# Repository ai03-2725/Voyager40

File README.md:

# Voyager40
A compact, fully featured 40% PCB

[Supported layouts](http://www.keyboard-layout-editor.com/#/gists/b095690facf5e7ddff7d799d73baacf5)  

#### In light of recent claims that I am 100% liable for any of my open source PCBs, I am adding this disclaimer.
#### I provide these PCBs as a reference for designing keyboard PCBs. Using them within your projects will require a will to do research of one's own and to learn the workings of them, potentially fixing issues if they exist.
# I provide these PCBs without liability and without any guarantees regarding functionality, as expressed in the MIT license under which all of these PCBs are licensed.

### Features
* In-switch LED backlighting
* RGB underglow
* Decent amount of layout compatibility
* Over-current and static discharge protection
* Fully open-source

### The Voyager PCB Family
The Voyager PCBs offer fully featured PCBs fit for any keyboard, whether mass production or high-end.

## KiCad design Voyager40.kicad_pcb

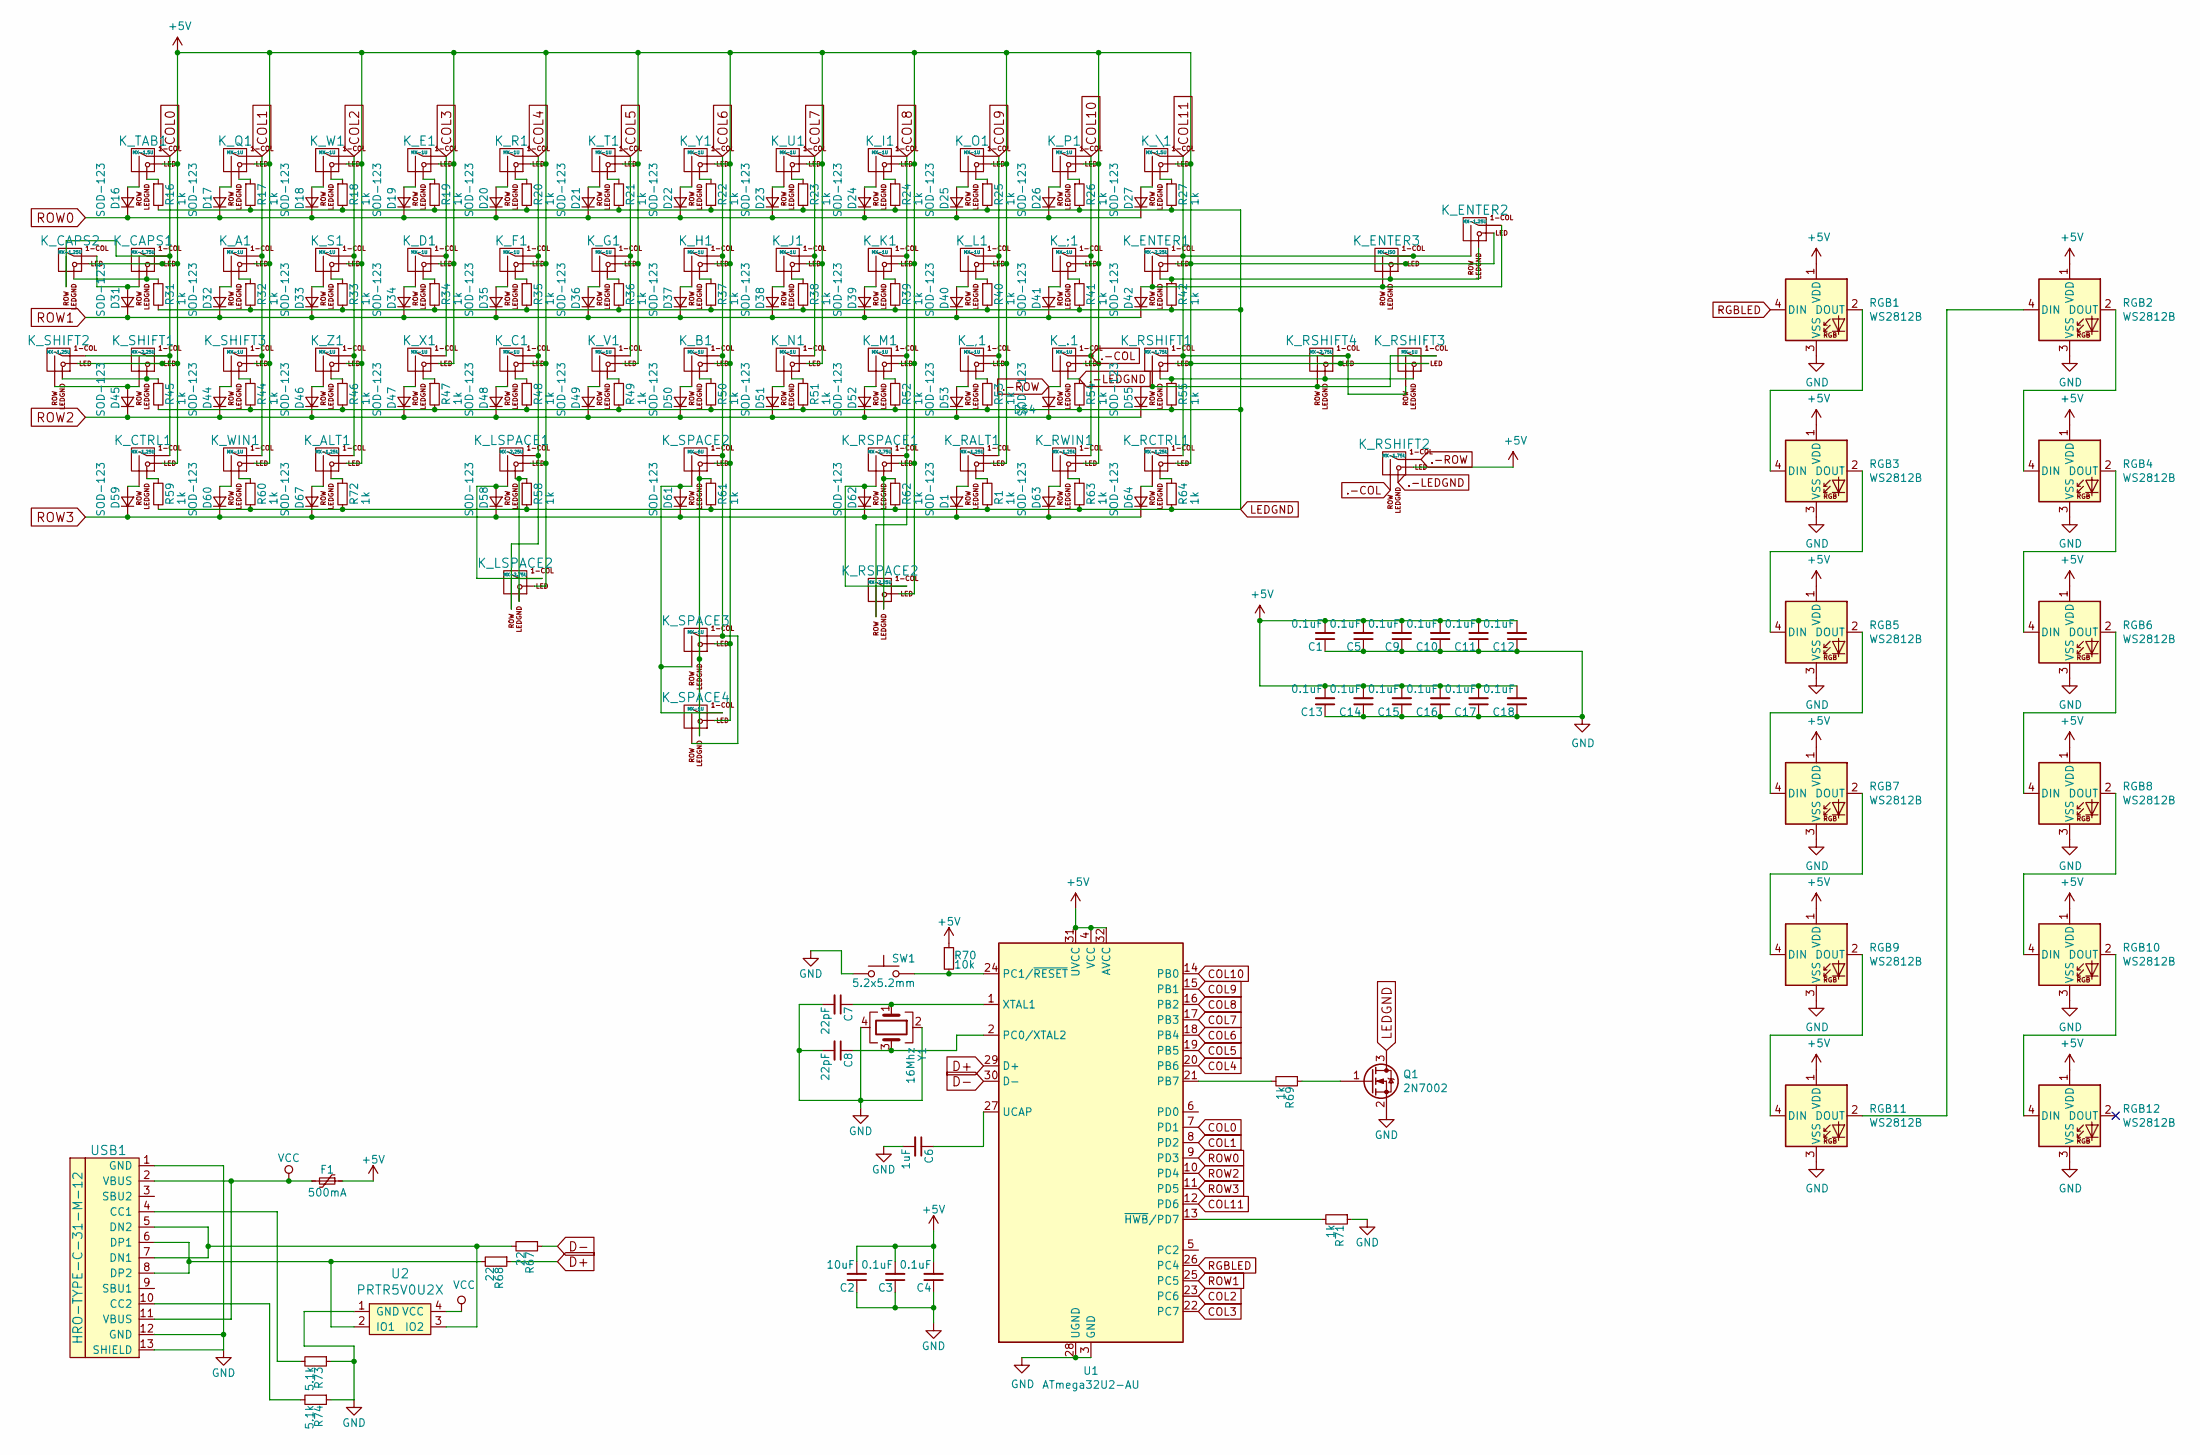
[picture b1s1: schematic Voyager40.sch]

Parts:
C1, C3, C4, C5, C9, C10, C11, C12, C13, C14, C15, C16, C17, C18: 0.1uF; C_0603
C2: 10uF; C_0603
C6: 1uF; C_0603
C7, C8: 22pF; C_0603
D1, D16, D17, D18, D19, D20, D21, D22, D23, D24, D25, D26, D27, D31, D32, D33, D34, D35, D36, D37, D38, D39, D40, D41, D42, D44, D45, D46, D47, D48, D49, D50, D51, D52, D53, D54, D55, D58, D59, D60, D61, D62, D63, D64, D67: SOD-123; D_SOD-123
F1: 500mA; Fuse_SMD1206_Reflow
K_,1: MX-1U
K_.1: MX-1U
K_;1: MX-1U
K_A1: MX-1U
K_ALT1: MX-1.25U
K_B1: MX-1U
K_C1: MX-1U
K_CAPS1: MX-1.75U
K_CAPS2: MX-1.25U; MX-1.25U-FLIPPED
K_CTRL1: MX-1.25U
K_D1: MX-1U
K_E1: MX-1U
K_ENTER1: MX-2.25U
K_ENTER2: MX-1.25U
K_ENTER3: MX-ISO; MX-ISO-ReversedStabilizers
K_F1: MX-1U
K_G1: MX-1U
K_H1: MX-1U
K_I1: MX-1U
K_J1: MX-1U
K_K1: MX-1U
K_L1: MX-1U
K_LSPACE1: MX-2.25U; MX-2.25U-ReversedStabilizers
K_LSPACE2: MX-2.75U; MX-2.75U-FLIPPED-ReversedStabilizers
K_M1: MX-1U
K_N1: MX-1U
K_O1: MX-1U
K_P1: MX-1U
K_Q1: MX-1U
K_R1: MX-1U
K_RALT1: MX-1.25U
K_RCTRL1: MX-1.25U
K_RSHIFT1, K_RSHIFT2: MX-1.75U
K_RSHIFT3: MX-1U
K_RSHIFT4: MX-2.75U
K_RSPACE1: MX-2.75U; MX-2.75U-ReversedStabilizers
K_RSPACE2: MX-2.25U; MX-2.25U-FLIPPED-ReversedStabilizers
K_RWIN1: MX-1.25U; MX-1U
K_S1: MX-1U
K_SHIFT1: MX-2.25U
K_SHIFT2: MX-1.25U
K_SHIFT3: MX-1U
K_SPACE2: MX-6U; MX-6U-ReversedStabilizers
K_SPACE3: MX-1U
K_SPACE4: MX-1U; MX-1U-FLIPPED
K_T1: MX-1U
K_TAB1: MX-1.5U
K_U1: MX-1U
K_V1: MX-1U
K_W1: MX-1U
K_WIN1: MX-1U
K_X1: MX-1U
K_Y1: MX-1U
K_Z1: MX-1U
K_\1: MX-1.5U
Q1: 2N7002; SOT-23
R1, R16, R17, R18, R19, R20, R21, R22, R23, R24, R25, R26, R27, R31, R32, R33, R34, R35, R36, R37, R38, R39, R40, R41, R42, R44, R45, R46, R47, R48, R49, R50, R51, R52, R53, R54, R55, R58, R59, R60, R61, R62, R63, R64, R69, R71, R72: 1k; R_0805
R67, R68: 22; R_0805
R70: 10k; R_0805
R73, R74: 5.1k; R_0805
RGB1, RGB2, RGB3, RGB4, RGB5, RGB6, RGB7, RGB8, RGB9, RGB10, RGB11, RGB12: WS2812B; LED_WS2812B-PLCC4
SW1: 5.2x5.2mm; SKQGADE010
U1: ATmega32U2-AU; QFN-32-1EP_5x5mm_Pitch0.5mm
U2: PRTR5V0U2X; SOT143B
USB1: HRO-TYPE-C-31-M-12; HRO-TYPE-C-31-M-12-Assembly
Y1: 16Mhz; Crystal_SMD_3225-4pin_3.2x2.5mm

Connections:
+5V: C1.2, C2.2, C3.2, C4.2, C5.2, C9.2, C10.2, C11.2, C12.2, C13.2, C14.2, C15.2, C16.2, C17.2, C18.2, F1.1, K_,1.3 (LED), K_.1.3 (LED), K_;1.3 (LED), K_A1.3 (LED), K_ALT1.3 (LED), K_B1.3 (LED), K_C1.3 (LED), K_CAPS1.3 (LED), K_CAPS2.3 (LED), K_CTRL1.3 (LED), K_D1.3 (LED), K_E1.3 (LED), K_ENTER1.3 (LED), K_ENTER2.3 (LED), K_ENTER3.3 (LED), K_F1.3 (LED), K_G1.3 (LED), K_H1.3 (LED), K_I1.3 (LED), K_J1.3 (LED), K_K1.3 (LED), K_L1.3 (LED), K_LSPACE1.3 (LED), K_LSPACE2.3 (LED), K_M1.3 (LED), K_N1.3 (LED), K_O1.3 (LED), K_P1.3 (LED), K_Q1.3 (LED), K_R1.3 (LED), K_RALT1.3 (LED), K_RCTRL1.3 (LED), K_RSHIFT1.3 (LED), K_RSHIFT2.3 (LED), K_RSHIFT3.3 (LED), K_RSHIFT4.3 (LED), K_RSPACE1.3 (LED), K_RSPACE2.3 (LED), K_RWIN1.3 (LED), K_S1.3 (LED), K_SHIFT1.3 (LED), K_SHIFT2.3 (LED), K_SHIFT3.3 (LED), K_SPACE2.3 (LED), K_SPACE3.3 (LED), K_SPACE4.3 (LED), K_T1.3 (LED), K_TAB1.3 (LED), K_U1.3 (LED), K_V1.3 (LED), K_W1.3 (LED), K_WIN1.3 (LED), K_X1.3 (LED), K_Y1.3 (LED), K_Z1.3 (LED), K_\1.3 (LED), R70.1, RGB1.1 (VDD), RGB2.1 (VDD), RGB3.1 (VDD), RGB4.1 (VDD), RGB5.1 (VDD), RGB6.1 (VDD), RGB7.1 (VDD), RGB8.1 (VDD), RGB9.1 (VDD), RGB10.1 (VDD), RGB11.1 (VDD), RGB12.1 (VDD), U1.4 (VCC), U1.31 (UVCC), U1.32 (AVCC)
.-COL: K_.1.1 (COL), K_;1.1 (COL), K_P1.1 (COL), K_RSHIFT2.2 (ROW), K_RWIN1.1 (COL), U1.14 (PB0)
.-LEDGND: K_.1.4 (LEDGND), K_RSHIFT2.4 (LEDGND), R54.1
.-ROW: D54.2 (A), K_.1.2 (ROW), K_RSHIFT2.1 (COL)
COL0: K_CAPS1.1 (COL), K_CAPS2.2 (ROW), K_CTRL1.1 (COL), K_SHIFT1.1 (COL), K_SHIFT2.1 (COL), K_TAB1.1 (COL), U1.7 (PD1)
COL1: K_A1.1 (COL), K_Q1.1 (COL), K_SHIFT3.1 (COL), K_WIN1.1 (COL), U1.8 (PD2)
COL2: K_ALT1.1 (COL), K_S1.1 (COL), K_W1.1 (COL), K_Z1.1 (COL), U1.23 (PC6)
COL3: K_D1.1 (COL), K_E1.1 (COL), K_X1.1 (COL), U1.22 (PC7)
COL4: K_C1.1 (COL), K_F1.1 (COL), K_LSPACE1.1 (COL), K_LSPACE2.2 (ROW), K_R1.1 (COL), U1.20 (PB6)
COL5: K_G1.1 (COL), K_T1.1 (COL), K_V1.1 (COL), U1.19 (PB5)
COL6: K_B1.1 (COL), K_H1.1 (COL), K_SPACE2.1 (COL), K_SPACE3.1 (COL), K_SPACE4.2 (ROW), K_Y1.1 (COL), U1.18 (PB4)
COL7: K_J1.1 (COL), K_N1.1 (COL), K_U1.1 (COL), U1.17 (PB3)
COL8: K_I1.1 (COL), K_K1.1 (COL), K_M1.1 (COL), K_RSPACE1.1 (COL), K_RSPACE2.2 (ROW), U1.16 (PB2)
COL9: K_,1.1 (COL), K_L1.1 (COL), K_O1.1 (COL), K_RALT1.1 (COL), U1.15 (PB1)
COL11: K_ENTER1.1 (COL), K_ENTER2.2 (ROW), K_ENTER3.1 (COL), K_RCTRL1.1 (COL), K_RSHIFT1.1 (COL), K_RSHIFT3.2 (ROW), K_RSHIFT4.1 (COL), K_\1.1 (COL), U1.12 (PD6)
D+: R68.1, U1.29 (D+)
D-: R67.1, U1.30 (D-)
GND: C1.1, C2.1, C3.1, C4.1, C5.1, C6.2, C7.2, C8.2, C9.1, C10.1, C11.1, C12.1, C13.1, C14.1, C15.1, C16.1, C17.1, C18.1, Q1.2 (S), R71.1, R73.1, R74.1, RGB1.3 (VSS), RGB2.3 (VSS), RGB3.3 (VSS), RGB4.3 (VSS), RGB5.3 (VSS), RGB6.3 (VSS), RGB7.3 (VSS), RGB8.3 (VSS), RGB9.3 (VSS), RGB10.3 (VSS), RGB11.3 (VSS), RGB12.3 (VSS), SW1.1, U1.3 (GND), U1.28 (UGND), U2.1 (GND), USB1.1 (GND), USB1.12 (GND), USB1.13 (SHIELD), Y1.2, Y1.4
LEDGND: Q1.3 (D), R1.2, R16.2, R17.2, R18.2, R19.2, R20.2, R21.2, R22.2, R23.2, R24.2, R25.2, R26.2, R27.2, R31.2, R32.2, R33.2, R34.2, R35.2, R36.2, R37.2, R38.2, R39.2, R40.2, R41.2, R42.2, R44.2, R45.2, R46.2, R47.2, R48.2, R49.2, R50.2, R51.2, R52.2, R53.2, R54.2, R55.2, R58.2, R59.2, R60.2, R61.2, R62.2, R63.2, R64.2, R72.2
unnamed: C6.1, U1.27 (UCAP)
unnamed: C7.1, U1.1 (XTAL1), Y1.1
unnamed: C8.1, U1.2 (PC0/XTAL2), Y1.3
unnamed: D1.2 (A), K_RALT1.2 (ROW)
unnamed: D16.2 (A), K_TAB1.2 (ROW)
unnamed: D17.2 (A), K_Q1.2 (ROW)
unnamed: D18.2 (A), K_W1.2 (ROW)
unnamed: D19.2 (A), K_E1.2 (ROW)
unnamed: D20.2 (A), K_R1.2 (ROW)
unnamed: D21.2 (A), K_T1.2 (ROW)
unnamed: D22.2 (A), K_Y1.2 (ROW)
unnamed: D23.2 (A), K_U1.2 (ROW)
unnamed: D24.2 (A), K_I1.2 (ROW)
unnamed: D25.2 (A), K_O1.2 (ROW)
unnamed: D26.2 (A), K_P1.2 (ROW)
unnamed: D27.2 (A), K_\1.2 (ROW)
unnamed: D31.2 (A), K_CAPS1.2 (ROW), K_CAPS2.1 (COL)
unnamed: D32.2 (A), K_A1.2 (ROW)
unnamed: D33.2 (A), K_S1.2 (ROW)
unnamed: D34.2 (A), K_D1.2 (ROW)
unnamed: D35.2 (A), K_F1.2 (ROW)
unnamed: D36.2 (A), K_G1.2 (ROW)
unnamed: D37.2 (A), K_H1.2 (ROW)
unnamed: D38.2 (A), K_J1.2 (ROW)
unnamed: D39.2 (A), K_K1.2 (ROW)
unnamed: D40.2 (A), K_L1.2 (ROW)
unnamed: D41.2 (A), K_;1.2 (ROW)
unnamed: D42.2 (A), K_ENTER1.2 (ROW), K_ENTER2.1 (COL), K_ENTER3.2 (ROW)
unnamed: D44.2 (A), K_SHIFT3.2 (ROW)
unnamed: D45.2 (A), K_SHIFT1.2 (ROW), K_SHIFT2.2 (ROW)
unnamed: D46.2 (A), K_Z1.2 (ROW)
unnamed: D47.2 (A), K_X1.2 (ROW)
unnamed: D48.2 (A), K_C1.2 (ROW)
unnamed: D49.2 (A), K_V1.2 (ROW)
unnamed: D50.2 (A), K_B1.2 (ROW)
unnamed: D51.2 (A), K_N1.2 (ROW)
unnamed: D52.2 (A), K_M1.2 (ROW)
unnamed: D53.2 (A), K_,1.2 (ROW)
unnamed: D55.2 (A), K_RSHIFT1.2 (ROW), K_RSHIFT3.1 (COL), K_RSHIFT4.2 (ROW)
unnamed: D58.2 (A), K_LSPACE1.2 (ROW), K_LSPACE2.1 (COL)
unnamed: D59.2 (A), K_CTRL1.2 (ROW)
unnamed: D60.2 (A), K_WIN1.2 (ROW)
unnamed: D61.2 (A), K_SPACE2.2 (ROW), K_SPACE3.2 (ROW), K_SPACE4.1 (COL)
unnamed: D62.2 (A), K_RSPACE1.2 (ROW), K_RSPACE2.1 (COL)
unnamed: D63.2 (A), K_RWIN1.2 (ROW)
unnamed: D64.2 (A), K_RCTRL1.2 (ROW)
unnamed: D67.2 (A), K_ALT1.2 (ROW)
unnamed: K_,1.4 (LEDGND), R53.1
unnamed: K_;1.4 (LEDGND), R41.1
unnamed: K_A1.4 (LEDGND), R32.1
unnamed: K_ALT1.4 (LEDGND), R72.1
unnamed: K_B1.4 (LEDGND), R50.1
unnamed: K_C1.4 (LEDGND), R48.1
unnamed: K_CAPS1.4 (LEDGND), K_CAPS2.4 (LEDGND), R31.1
unnamed: K_CTRL1.4 (LEDGND), R59.1
unnamed: K_D1.4 (LEDGND), R34.1
unnamed: K_E1.4 (LEDGND), R19.1
unnamed: K_ENTER1.4 (LEDGND), K_ENTER2.4 (LEDGND), K_ENTER3.4 (LEDGND), R42.1
unnamed: K_F1.4 (LEDGND), R35.1
unnamed: K_G1.4 (LEDGND), R36.1
unnamed: K_H1.4 (LEDGND), R37.1
unnamed: K_I1.4 (LEDGND), R24.1
unnamed: K_J1.4 (LEDGND), R38.1
unnamed: K_K1.4 (LEDGND), R39.1
unnamed: K_L1.4 (LEDGND), R40.1
unnamed: K_LSPACE1.4 (LEDGND), K_LSPACE2.4 (LEDGND), R58.1
unnamed: K_M1.4 (LEDGND), R52.1
unnamed: K_N1.4 (LEDGND), R51.1
unnamed: K_O1.4 (LEDGND), R25.1
unnamed: K_P1.4 (LEDGND), R26.1
unnamed: K_Q1.4 (LEDGND), R17.1
unnamed: K_R1.4 (LEDGND), R20.1
unnamed: K_RALT1.4 (LEDGND), R1.1
unnamed: K_RCTRL1.4 (LEDGND), R64.1
unnamed: K_RSHIFT1.4 (LEDGND), K_RSHIFT3.4 (LEDGND), K_RSHIFT4.4 (LEDGND), R55.1
unnamed: K_RSPACE1.4 (LEDGND), K_RSPACE2.4 (LEDGND), R62.1
unnamed: K_RWIN1.4 (LEDGND), R63.1
unnamed: K_S1.4 (LEDGND), R33.1
unnamed: K_SHIFT1.4 (LEDGND), K_SHIFT2.4 (LEDGND), R45.1
unnamed: K_SHIFT3.4 (LEDGND), R44.1
unnamed: K_SPACE2.4 (LEDGND), K_SPACE3.4 (LEDGND), K_SPACE4.4 (LEDGND), R61.1
unnamed: K_T1.4 (LEDGND), R21.1
unnamed: K_TAB1.4 (LEDGND), R16.1
unnamed: K_U1.4 (LEDGND), R23.1
unnamed: K_V1.4 (LEDGND), R49.1
unnamed: K_W1.4 (LEDGND), R18.1
unnamed: K_WIN1.4 (LEDGND), R60.1
unnamed: K_X1.4 (LEDGND), R47.1
unnamed: K_Y1.4 (LEDGND), R22.1
unnamed: K_Z1.4 (LEDGND), R46.1
unnamed: K_\1.4 (LEDGND), R27.1
unnamed: Q1.1 (G), R69.1
unnamed: R67.2, U2.3 (IO2), USB1.5 (DN2), USB1.7 (DN1)
unnamed: R68.2, U2.2 (IO1), USB1.6 (DP1), USB1.8 (DP2)
unnamed: R69.2, U1.21 (PB7)
unnamed: R70.2, SW1.2, U1.24 (PC1/~RESET)
unnamed: R71.2, U1.13 (~HWB~/PD7)
unnamed: R73.2, USB1.4 (CC1)
unnamed: R74.2, USB1.10 (CC2)
unnamed: RGB1.2 (DOUT), RGB3.4 (DIN)
unnamed: RGB2.2 (DOUT), RGB4.4 (DIN)
unnamed: RGB3.2 (DOUT), RGB5.4 (DIN)
unnamed: RGB4.2 (DOUT), RGB6.4 (DIN)
unnamed: RGB5.2 (DOUT), RGB7.4 (DIN)
unnamed: RGB6.2 (DOUT), RGB8.4 (DIN)
unnamed: RGB7.2 (DOUT), RGB9.4 (DIN)
unnamed: RGB10.2 (DOUT), RGB12.4 (DIN)
unnamed: RGB8.2 (DOUT), RGB10.4 (DIN)
unnamed: RGB2.4 (DIN), RGB11.2 (DOUT)
unnamed: RGB9.2 (DOUT), RGB11.4 (DIN)
RGBLED: RGB1.4 (DIN), U1.26 (PC4)
ROW0: D16.1 (K), D17.1 (K), D18.1 (K), D19.1 (K), D20.1 (K), D21.1 (K), D22.1 (K), D23.1 (K), D24.1 (K), D25.1 (K), D26.1 (K), D27.1 (K), U1.9 (PD3)
ROW1: D31.1 (K), D32.1 (K), D33.1 (K), D34.1 (K), D35.1 (K), D36.1 (K), D37.1 (K), D38.1 (K), D39.1 (K), D40.1 (K), D41.1 (K), D42.1 (K), U1.25 (PC5)
ROW2: D44.1 (K), D45.1 (K), D46.1 (K), D47.1 (K), D48.1 (K), D49.1 (K), D50.1 (K), D51.1 (K), D52.1 (K), D53.1 (K), D54.1 (K), D55.1 (K), U1.10 (PD4)
ROW3: D1.1 (K), D58.1 (K), D59.1 (K), D60.1 (K), D61.1 (K), D62.1 (K), D63.1 (K), D64.1 (K), D67.1 (K), U1.11 (PD5)
VCC: F1.2, U2.4 (VCC), USB1.2 (VBUS), USB1.11 (VBUS)

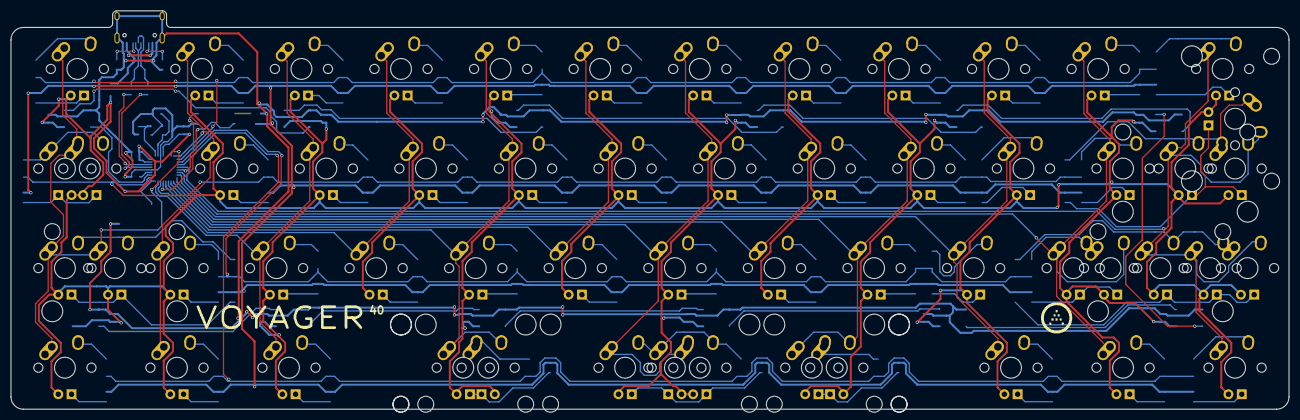
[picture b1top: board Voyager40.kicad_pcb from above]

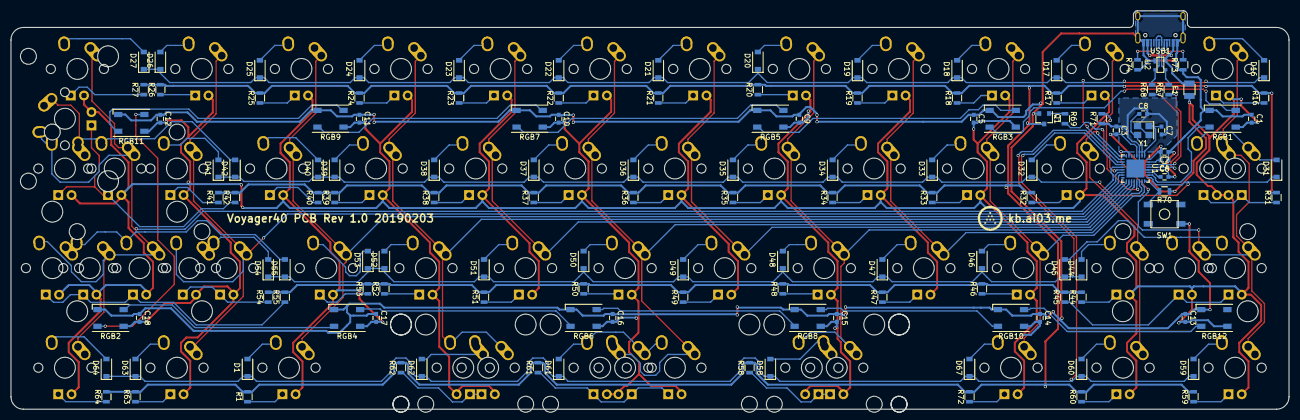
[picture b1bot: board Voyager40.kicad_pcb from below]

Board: 2 copper layers, 244.5 x 76.2 mm, 190 parts (134 on the bottom side), 135 nets.

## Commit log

2019-02-02 Add submodules
2019-02-03 Finish up project
2019-02-03 Add render
2019-02-03 Add layouts
2019-02-17 Initial STM32F072CB replacement
2019-02-17 Produce new gerbers
2019-02-18 Progress save
2019-02-18 Reroute
2019-02-18 Add logo
2019-04-16 Repair the column traces
